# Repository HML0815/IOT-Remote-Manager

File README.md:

# IOT-Remote-Manager
Capstone Project for Technical Project Fall 2026

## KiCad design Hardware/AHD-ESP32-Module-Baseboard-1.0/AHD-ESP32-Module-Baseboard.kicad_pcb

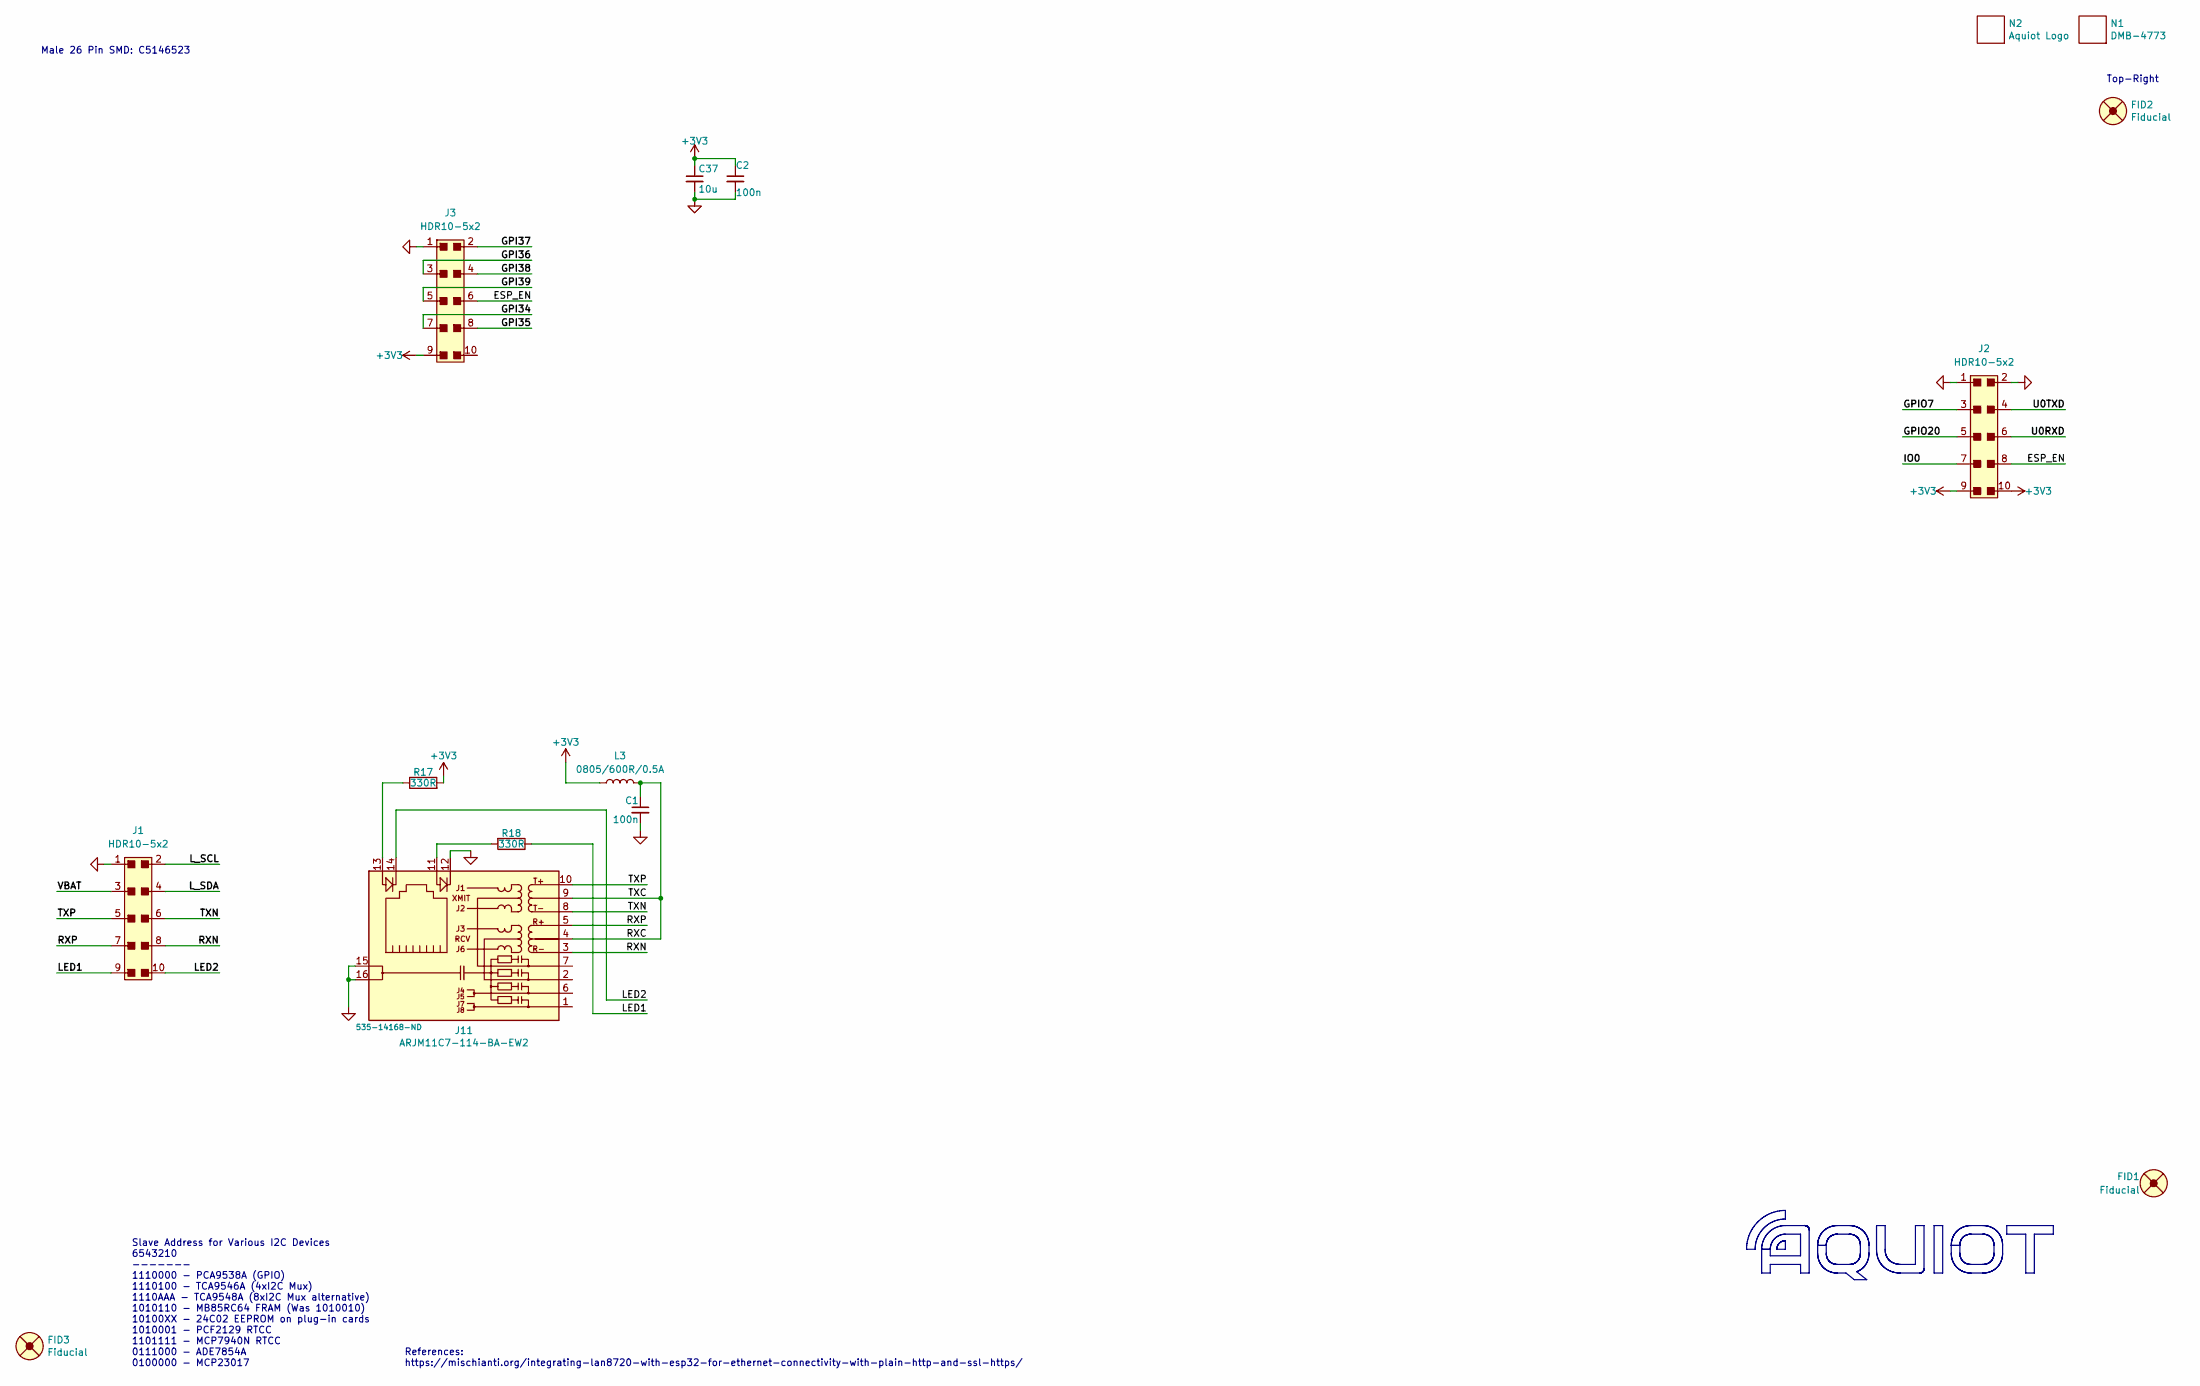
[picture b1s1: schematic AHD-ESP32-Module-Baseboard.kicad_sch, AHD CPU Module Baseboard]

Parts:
C1, C2: 100n; C_0603_1608Metric; LCSC C14663
C37: 10u; C_0603_1608Metric; LCSC C96446
FID1, FID2, FID3: Fiducial; Fiducial_1mm_Dia_2.54mm_Outer_CopperTop; JLC DNP
J1, J2, J3: HDR10-5x2; Pin_Socket_Straight_2x05_Pitch2.54mm_60milPad
J11: ARJM11C7-114-BA-EW2; JLC DNP
L3: 0805/600R/0.5A; L_0805_2012Metric; LCSC C1017
N1: DMB-4773; Bud-DMB-4773; JLC DNP
N2: Aquiot Logo; Aquiot-Logo-2024-500mil; JLC DNP
R17, R18: 330R; R_0603_1608Metric; LCSC C23138

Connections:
+3V3: C2.1, C37.1, J2.9, J2.10, J3.9, L3.1, R17.2
/ESP_EN: J2.8, J3.6
/GPI34: J3.7
/GPI35: J3.8
/GPI36: J3.3
/GPI37: J3.2
/GPI38: J3.4
/GPI39: J3.5
/GPIO7: J2.3
/GPIO20: J2.5
/IO0: J2.7
/LED1: J1.9, R18.1
/LED2: J1.10, J11.14
/L_SCL: J1.2
/L_SDA: J1.4
/RXC: C1.1, J11.4 (CT), J11.9 (CT), L3.2
/RXN: J1.8, J11.3 (RD-)
/RXP: J1.7, J11.5 (RD+)
/TXN: J1.6, J11.8 (TD-)
/TXP: J1.5, J11.10 (TD+)
/U0RXD: J2.6
/U0TXD: J2.4
/VBAT: J1.3
GND: C1.2, C2.2, C37.2, J1.1, J2.1, J2.2, J3.1, J11.12, J11.15, J11.16
unnamed: J11.11, R18.2
unnamed: J11.13, R17.1

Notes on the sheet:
References: https://mischianti.org/integrating-lan8720-with-esp32-for-ethernet-connectivity-with-plain-http-and-ssl-https/
Slave Address for Various I2C Devices 6543210 ------- 1110000 - PCA9538A (GPIO) 1110100 - TCA9546A (4xI2C Mux) 1110AAA - TCA9548A (8xI2C Mux alternative) 1010110 - MB85RC64 FRAM (Was 1010010) 10100XX - 24C02 EEPROM on plug-in cards 1010001 - PCF2129 RTCC 1101111 - MCP7940N RTCC 0111000 - ADE7854A 0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
Male 26 Pin SMD: C5146523
Top-Right

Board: 2 copper layers, 15 parts (0 on the bottom side), 12 nets, no tracks yet.

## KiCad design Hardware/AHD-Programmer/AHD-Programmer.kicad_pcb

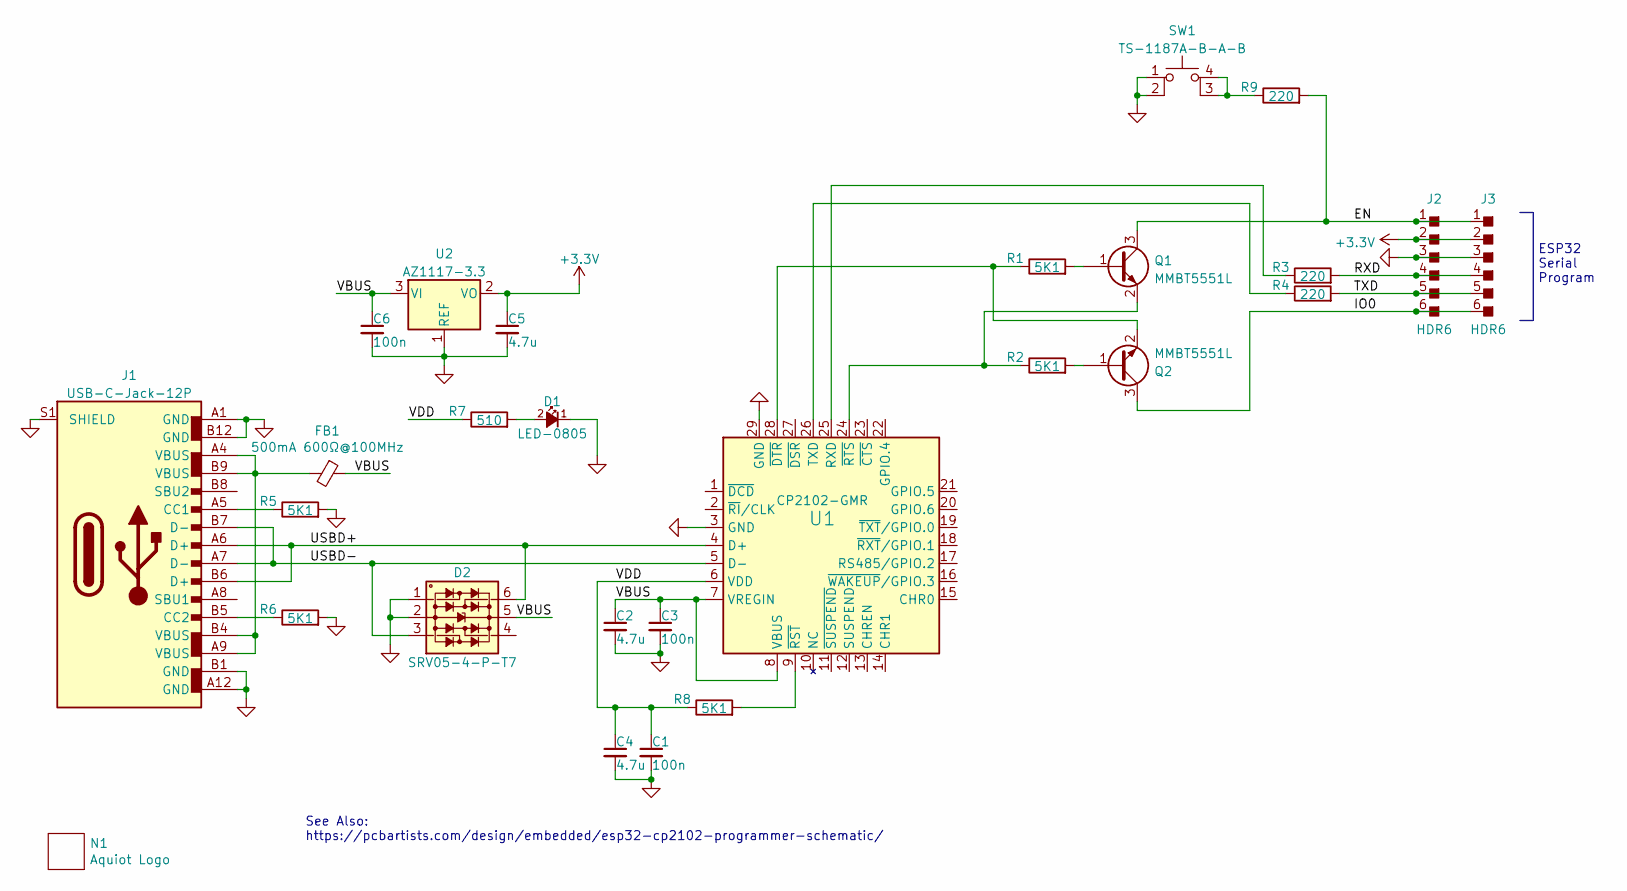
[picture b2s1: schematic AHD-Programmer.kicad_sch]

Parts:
C1, C3, C6: 100n; C_0603_1608Metric; JLC C14663
C2, C4, C5: 4.7u; C_0603_1608Metric; JLC C19666
D1: LED-0805; LED_0805_2012Metric; JLC C84256
D2: SRV05-4-P-T7; SOT-23-6; JLC C85364
FB1: 500mA 600Ω@100MHz; L_0805_2012Metric; JLC C1017
J1: USB-C-Jack-12P; USB-C-TYPE-C-31-M-12; JLC C165948
J2, J3: HDR6; Pin_Header_Straight_1x06_Pitch2.54mm
N1: Aquiot Logo; Aquiot-Logo-6.5mm; JLC DNP
Q1, Q2: MMBT5551L; SOT-23; JLC C2145
R1, R2, R5, R6, R8: 5K1; R_0603_1608Metric; JLC C23186
R3, R4, R9: 220; R_0603_1608Metric; JLC C22962
R7: 510; R_0603_1608Metric; JLC C23193
SW1: TS-1187A-B-A-B; PushButton-TS-1187A-B-A-B(C318884); JLC C318884
U1: CP2102-GMR; QFN-28-1EP_5x5mm_P0.5mm_EP3.35x3.35mm; JLC C6568
U2: AZ1117-3.3; SOT-223-3_TabPin2; JLC C6186

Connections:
+3.3V: C5.1, J2.2, J3.2, U2.2 (VO)
/EN: J2.1, J3.1, Q1.3 (C), R9.2
/IO0: J2.6, J3.6, Q2.3 (C)
/RXD: J2.4, J3.4, R3.2
/TXD: J2.5, J3.5, R4.2
/USBD+: D2.6 (I/O4), J1.A6 (D+), J1.B6 (D+), U1.4 (D+)
/USBD-: D2.3 (I/O2), J1.A7 (D-), J1.B7 (D-), U1.5 (D-)
/VBUS: C2.1, C3.1, C6.1, D2.5 (VCC), FB1.1, U1.7 (VREGIN), U1.8 (VBUS), U2.3 (VI)
/VDD: C1.1, C4.1, R7.1, R8.1, U1.6 (VDD)
GND: C1.2, C2.2, C3.2, C4.2, C5.2, C6.2, D1.1 (A), D2.1 (I/O1), D2.2 (GND), J1.A1 (GND), J1.A12 (GND), J1.B1 (GND), J1.B12 (GND), J1.S1 (SHIELD), J2.3, J3.3, R5.2, R6.2, SW1.1, SW1.2, U1.3 (GND), U1.29 (GND), U2.1 (REF)
unnamed: D1.2 (K), R7.2
unnamed: FB1.2, J1.A4 (VBUS), J1.A9 (VBUS), J1.B4 (VBUS), J1.B9 (VBUS)
unnamed: J1.A5 (CC1), R5.1
unnamed: J1.B5 (CC2), R6.1
unnamed: Q1.1 (B), R1.2
unnamed: Q1.2 (E), R2.1, U1.24 (~RTS)
unnamed: Q2.1 (B), R2.2
unnamed: Q2.2 (E), R1.1, U1.28 (~DTR)
unnamed: R3.1, U1.25 (RXD)
unnamed: R4.1, U1.26 (TXD)
unnamed: R8.2, U1.9 (~RST)
unnamed: R9.1, SW1.3 (K), SW1.4 (A)

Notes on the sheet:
See Also: https://pcbartists.com/design/embedded/esp32-cp2102-programmer-schematic/
ESP32 Serial Program

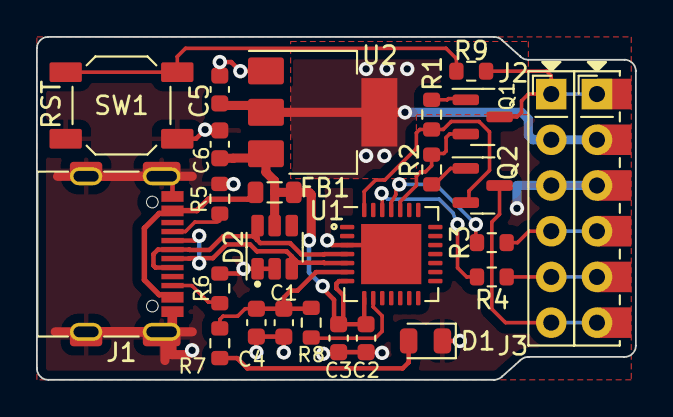
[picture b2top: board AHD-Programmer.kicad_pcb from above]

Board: 2 copper layers, 33.3 x 19.0 mm, 27 parts (1 on the bottom side), 22 nets.

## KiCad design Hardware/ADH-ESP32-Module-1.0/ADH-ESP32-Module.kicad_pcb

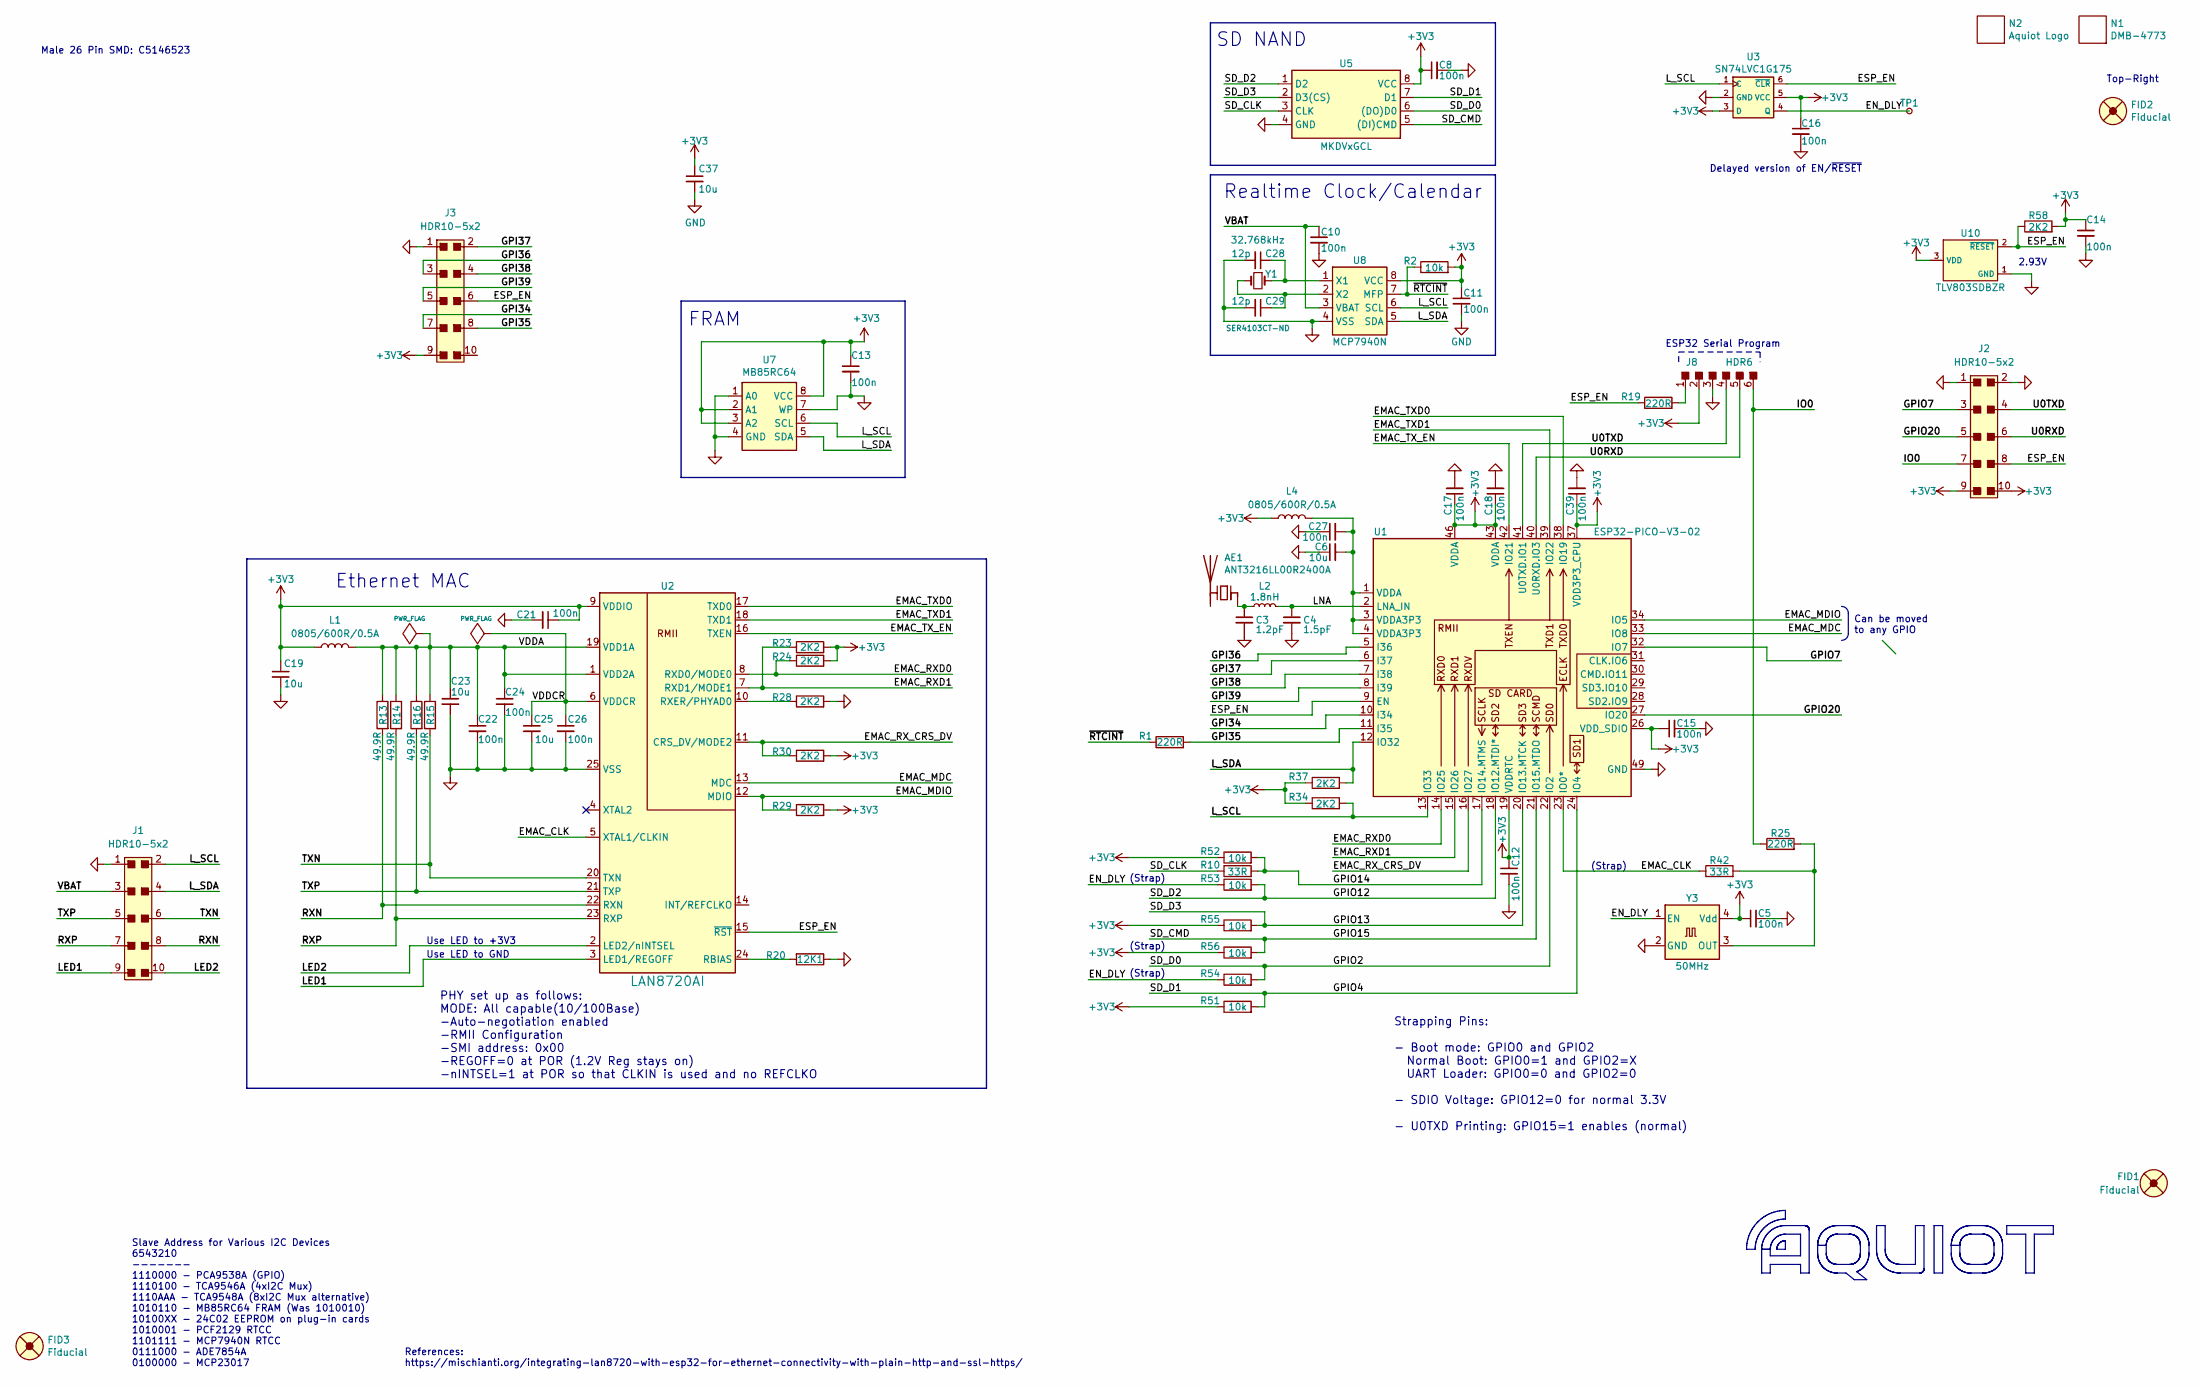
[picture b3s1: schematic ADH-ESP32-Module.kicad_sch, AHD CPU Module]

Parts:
AE1: ANT3216LL00R2400A
C3: 1.2pF; C_0402_1005Metric; LCSC C1551
C4: 1.5pF; C_0402_1005Metric; LCSC C1552
C5, C8, C10, C11, C12, C13, C14, C15, C16, C17, C18, C21, C22, C24, C26, C27, C39: 100n; C_0603_1608Metric; LCSC C14663
C6, C19, C23, C25, C37: 10u; C_0603_1608Metric; LCSC C96446
C28, C29: 12p; C_0603_1608Metric; LCSC C38523
FID1, FID2, FID3: Fiducial; Fiducial_1mm_Dia_2.54mm_Outer_CopperTop; JLC DNP
J1, J2, J3: HDR10-5x2; Pin_Header_Straight_2x05_Pitch2.54mm_60milPad-B
J8: HDR6; Pin_Header_Pressfit_1x06_Pitch2.54mm; JLC DNP
L1, L4: 0805/600R/0.5A; L_0805_2012Metric; LCSC C1017
L2: 1.8nH; L_0402_1005Metric; LCSC C77107
N1: DMB-4773; Bud-DMB-4773; JLC DNP
N2: Aquiot Logo; Aquiot-Logo-2024-500mil; JLC DNP
R1, R19, R25: 220R; R_0603_1608Metric; LCSC C22962
R2, R51, R52, R53, R54, R55, R56: 10k; R_0603_1608Metric; LCSC C25804
R10, R42: 33R; R_0603_1608Metric; LCSC C23140
R13, R14, R15, R16: 49.9R; R_0603_1608Metric; LCSC C23185
R20: 12K1; R_0603_1608Metric; LCSC C2930059
R23, R24, R28, R29, R30, R34, R37, R58: 2K2; R_0603_1608Metric; LCSC C4190
TP1: TestPoint; ProbePoint-THT-D1.0mm-Drill0.5mm
U1: ESP32-PICO-V3-02; QFN-48-ESP32-PICO-V3-02
U2: LAN8720AI; QFN-24-1EP_4x4mm_P0.5mm_EP2.6x2.6mm-JLC; JLC C17146
U3: SN74LVC1G175; SOT-363_SC-70-6; LCSC C202238
U5: MKDVxGCL; W-PDFN-8-8x6
U7: MB85RC64; SOIC-8_3.9x4.9mm_P1.27mm-JLC; LCSC C8740
U8: MCP7940N; SOIC-8_3.9x4.9mm_P1.27mm-JLC; JLC C51106
U10: TLV803SDBZR; SOT-23-JLC; LCSC C132016
Y1: 32.768kHz; Crystal_SMD_3215-2Pin_3.2x1.5mm; JLC C32346
Y3: 50MHz; SMD3225-4P; LCSC C5203552

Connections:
+3V3: C5.1, C8.1, C11.1, C12.1, C13.1, C14.1, C15.1, C16.1, C17.1, C18.1, C19.1, C21.1, C37.1, C39.1, J2.9, J2.10, J3.9, J8.2, L1.1, L4.1, R2.2, R23.2, R24.2, R29.2, R30.2, R34.1, R37.1, R51.1, R52.1, R55.1, R56.1, R58.2, U1.19 (VDDRTC), U1.26 (VDD_SDIO), U1.37 (VDD3P3_CPU), U1.43 (VDDA), U1.46 (VDDA), U2.9 (VDDIO), U3.3 (D), U3.5 (VCC), U5.8 (VCC), U7.2 (A1), U7.3 (A2), U7.8 (VCC), U8.8 (VCC), U10.3 (VDD), Y3.4 (Vdd)
/EMAC_CLK: R42.1, U1.23 (IO0*), U2.5 (XTAL1/CLKIN)
/EMAC_MDC: U1.33 (IO8), U2.13 (MDC)
/EMAC_MDIO: R29.1, U1.34 (IO5), U2.12 (MDIO)
/EMAC_RXD0: R24.1, U1.14 (IO25), U2.8 (RXD0/MODE0)
/EMAC_RXD1: R23.1, U1.15 (IO26), U2.7 (RXD1/MODE1)
/EMAC_RX_CRS_DV: R30.1, U1.16 (IO27), U2.11 (CRS_DV/MODE2)
/EMAC_TXD0: U1.38 (IO19), U2.17 (TXD0)
/EMAC_TXD1: U1.39 (IO22), U2.18 (TXD1)
/EMAC_TX_EN: U1.42 (IO21), U2.16 (TXEN)
/EN_DLY: R53.1, R54.1, TP1.1, U3.4 (Q), Y3.1 (EN)
/ESP_EN: J2.8, J3.6, R19.1, R58.1, U1.9 (EN), U2.15 (~RST), U3.6 (~CLR), U10.2 (~RESET)
/GPI34: J3.7, U1.10 (I34)
/GPI35: J3.8, R1.2, U1.11 (I35)
/GPI36: J3.3, U1.5 (I36)
/GPI37: J3.2, U1.6 (I37)
/GPI38: J3.4, U1.7 (I38)
/GPI39: J3.5, U1.8 (I39)
/GPIO2: R54.2, U1.22 (IO2), U5.6 ((DO)D0)
/GPIO4: R51.2, U1.24 (IO4), U5.7 (D1)
/GPIO7: J2.3, U1.32 (IO7)
/GPIO12: R53.2, U1.18 (IO12.MTDI*), U5.1 (D2)
/GPIO13: R55.2, U1.20 (IO13.MTCK), U5.2 (D3(CS))
/GPIO14: R10.2, R52.2, U1.17 (IO14.MTMS)
/GPIO15: R56.2, U1.21 (IO15.MTDO), U5.5 ((DI)CMD)
/GPIO20: J2.5, U1.27 (IO20)
/IO0: J2.7, J8.6, R25.1
/LED1: J1.9, U2.3 (LED1/REGOFF)
/LED2: J1.10, U2.2 (LED2/nINTSEL)
/LNA: C4.1, L2.2, U1.2 (LNA_IN)
/L_SCL: J1.2, R34.2, U1.13 (IO33), U3.1 (C), U7.6 (SCL), U8.6 (SCL)
/L_SDA: J1.4, R37.2, U1.12 (IO32), U7.5 (SDA), U8.5 (SDA)
/RXN: J1.8, R13.2, U2.22 (RXN)
/RXP: J1.7, R14.2, U2.23 (RXP)
/SD_CLK: R10.1, U5.3 (CLK)
/TXN: J1.6, R15.2, U2.20 (TXN)
/TXP: J1.5, R16.2, U2.21 (TXP)
/U0RXD: J2.6, J8.5, U1.40 (U0RXD.IO3)
/U0TXD: J2.4, J8.4, U1.41 (U0TXD.IO1)
/VBAT: C10.1, J1.3, U8.3 (VBAT)
/VDDA: C22.1, C23.1, C24.1, L1.2, R13.1, R14.1, R15.1, R16.1, U2.1 (VDD2A), U2.19 (VDD1A)
/VDDCR: C25.1, C26.1, U2.6 (VDDCR)
/~RTCINT: R1.1, R2.1, U8.7 (MFP)
GND: C3.2, C4.2, C5.2, C6.1, C8.2, C10.2, C11.2, C12.2, C13.2, C14.2, C15.2, C16.2, C17.2, C18.2, C19.2, C21.2, C22.2, C23.2, C24.2, C25.2, C26.2, C27.1, C28.2, C29.2, C37.2, C39.2, J1.1, J2.1, J2.2, J3.1, J8.3, R20.1, R28.2, U1.49 (GND), U2.25 (VSS), U3.2 (GND), U5.4 (GND), U7.1 (A0), U7.4 (GND), U7.7 (WP), U8.4 (VSS), U10.1 (GND), Y3.2 (GND)
unnamed: AE1.1 (FEED), C3.1, L2.1
unnamed: C6.2, C27.2, L4.2, U1.1 (VDDA), U1.3 (VDDA3P3), U1.4 (VDDA3P3)
unnamed: J8.1, R19.2
unnamed: R20.2, U2.24 (RBIAS)
unnamed: R28.1, U2.10 (RXER/PHYAD0)
unnamed: C28.1, U8.1 (X1), Y1.1
unnamed: C29.1, U8.2 (X2), Y1.2
unnamed: R25.2, R42.2, Y3.3 (OUT)

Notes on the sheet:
(Strap)
Use LED to +3V3
References: https://mischianti.org/integrating-lan8720-with-esp32-for-ethernet-connectivity-with-plain-http-and-ssl-https/
Realtime Clock/Calendar
2.93V
FRAM
Delayed version of EN/~{RESET}
Slave Address for Various I2C Devices 6543210 ------- 1110000 - PCA9538A (GPIO) 1110100 - TCA9546A (4xI2C Mux) 1110AAA - TCA9548A (8xI2C Mux alternative) 1010110 - MB85RC64 FRAM (Was 1010010) 10100XX - 24C02 EEPROM on plug-in cards 1010001 - PCF2129 RTCC 1101111 - MCP7940N RTCC 0111000 - ADE7854A 0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
PHY set up as follows: MODE: All capable(10/100Base) -Auto-negotiation enabled -RMII Configuration -SMI address: 0x00 -REGOFF=0 at POR (1.2V Reg stays on) -nINTSEL=1 at POR so that CLKIN is used and no REFCLKO
Male 26 Pin SMD: C5146523
ESP32 Serial Program
Top-Right
Use LED to GND
Ethernet MAC
Can be moved to any GPIO
Strapping Pins: - Boot mode: GPIO0 and GPIO2 Normal Boot: GPIO0=1 and GPIO2=X UART Loader: GPIO0=0 and GPIO2=0 - SDIO Voltage: GPIO12=0 for normal 3.3V - U0TXD Printing: GPIO15=1 enables (normal)
SD NAND

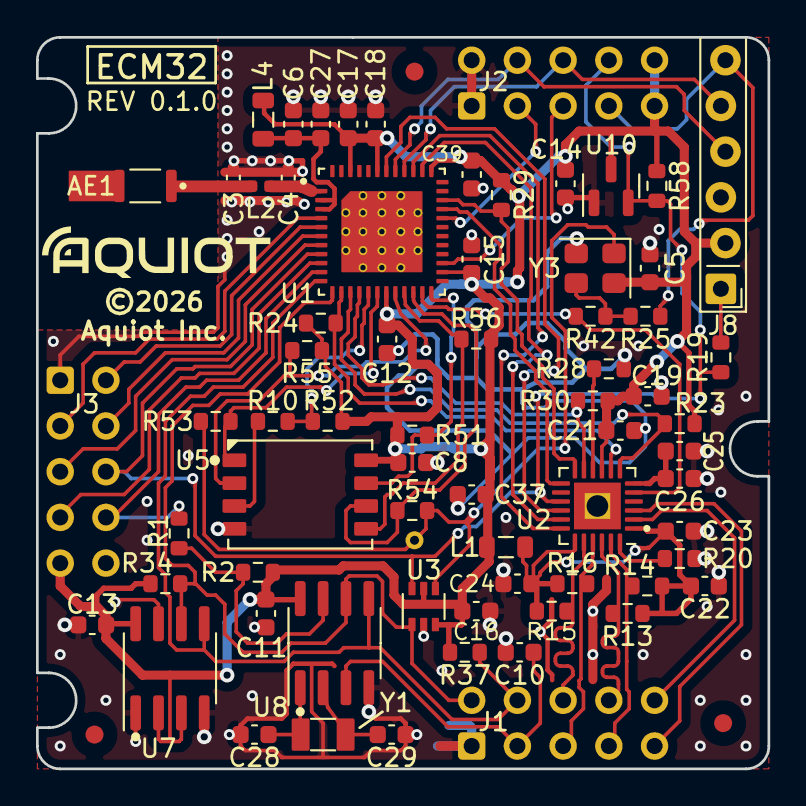
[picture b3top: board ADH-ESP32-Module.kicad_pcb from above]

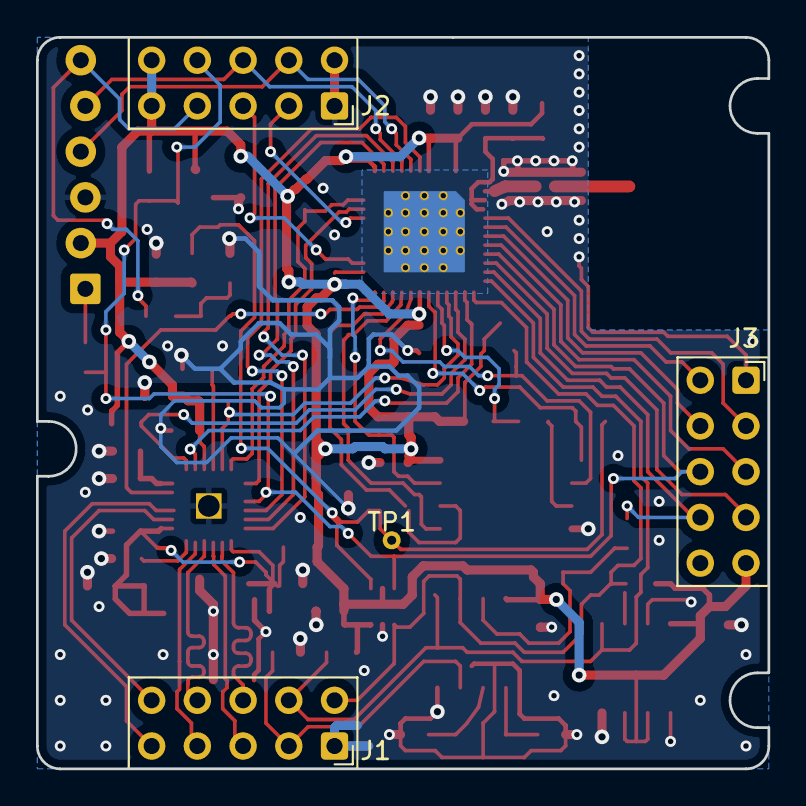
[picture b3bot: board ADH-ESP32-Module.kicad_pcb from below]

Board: 2 copper layers, 40.6 x 40.6 mm, 73 parts (4 on the bottom side), 52 nets.

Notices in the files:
Hardware/ADH-ESP32-Module-1.0/ADH-ESP32-Module.kicad_pcb:
©Aquiot Inc.
©2026
